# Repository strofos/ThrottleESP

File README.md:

# Z21 Throttle ESP
Z21 throttle implementation on ESP32 like a light Z21 lok maus. You might even build it on ESP8266 as there is no ESP32 specific functions used. It uses a standard variable resistor (pot) to handle the speed. Only 126 DCC steps is implemented. A 3x4 keyboard is used to navigate throw the menu and handle the functions 0 to 9. The code gets data from the Z21 asyncronous, so if you change the locomotive or the tracks gets an EStop you get notified on the throttle also. 

# Electronic Components
 1. ESP32 DEV board
 2. Nokia 5110 PCD8544 display module
 3. 5k or 10k variable resistor
 4. 3x4 keyboard
 5. 18650 single cell as power suply

# Flash the code
Use a standard Arduino IDE to flash the code. Just make sure you have the correct board selected and install the graphic libraries from Adafruit. I used a Nokia 5110 display, PCD8544 chipset, SPI driven, so is easy to adapt it to another SPI display.  

# Setup the Wifi
The wifi SSID and password are set inside the Config.h file. Just edit it and put your own settings.

# TCP commands
The IP can be found in the menu of the throttle, goto Menu (hold * for 1 sec) and then select Wifi (press 2). The default port is 5983. The open Putty, add the IP and port and then select Telnet. If successful a command promt will apear. You can now send the desired command to the throttle.
Here is the complete list of commands implemented on the throttle:
- &lt;loco adr="45"> -> lock the loco address to 45. change the 45 to the desired address
- &lt;loco adr="*">  -> unlock the loco address menu. the address can be changed
- &lt;lock>          -> locks the maus, all actions are suspended
- &lt;unlock>        -> unlocks/frees the maus; also <loco> commands can be used

# How to make the enclosure
After you print the Top and Bottom enclosure parts on a standard 3D filament printer you need some M3 insert-threads and M3 standard screws to put it all together. See the images for more information. I test-printed them on my Anycubic Kobra S1 3D printer. The 18650 cell lid is still under design so it is missing from the current repo.

# Copyright
Fell free to download, make and share this project! A like or share of this repo will be much appreciated!

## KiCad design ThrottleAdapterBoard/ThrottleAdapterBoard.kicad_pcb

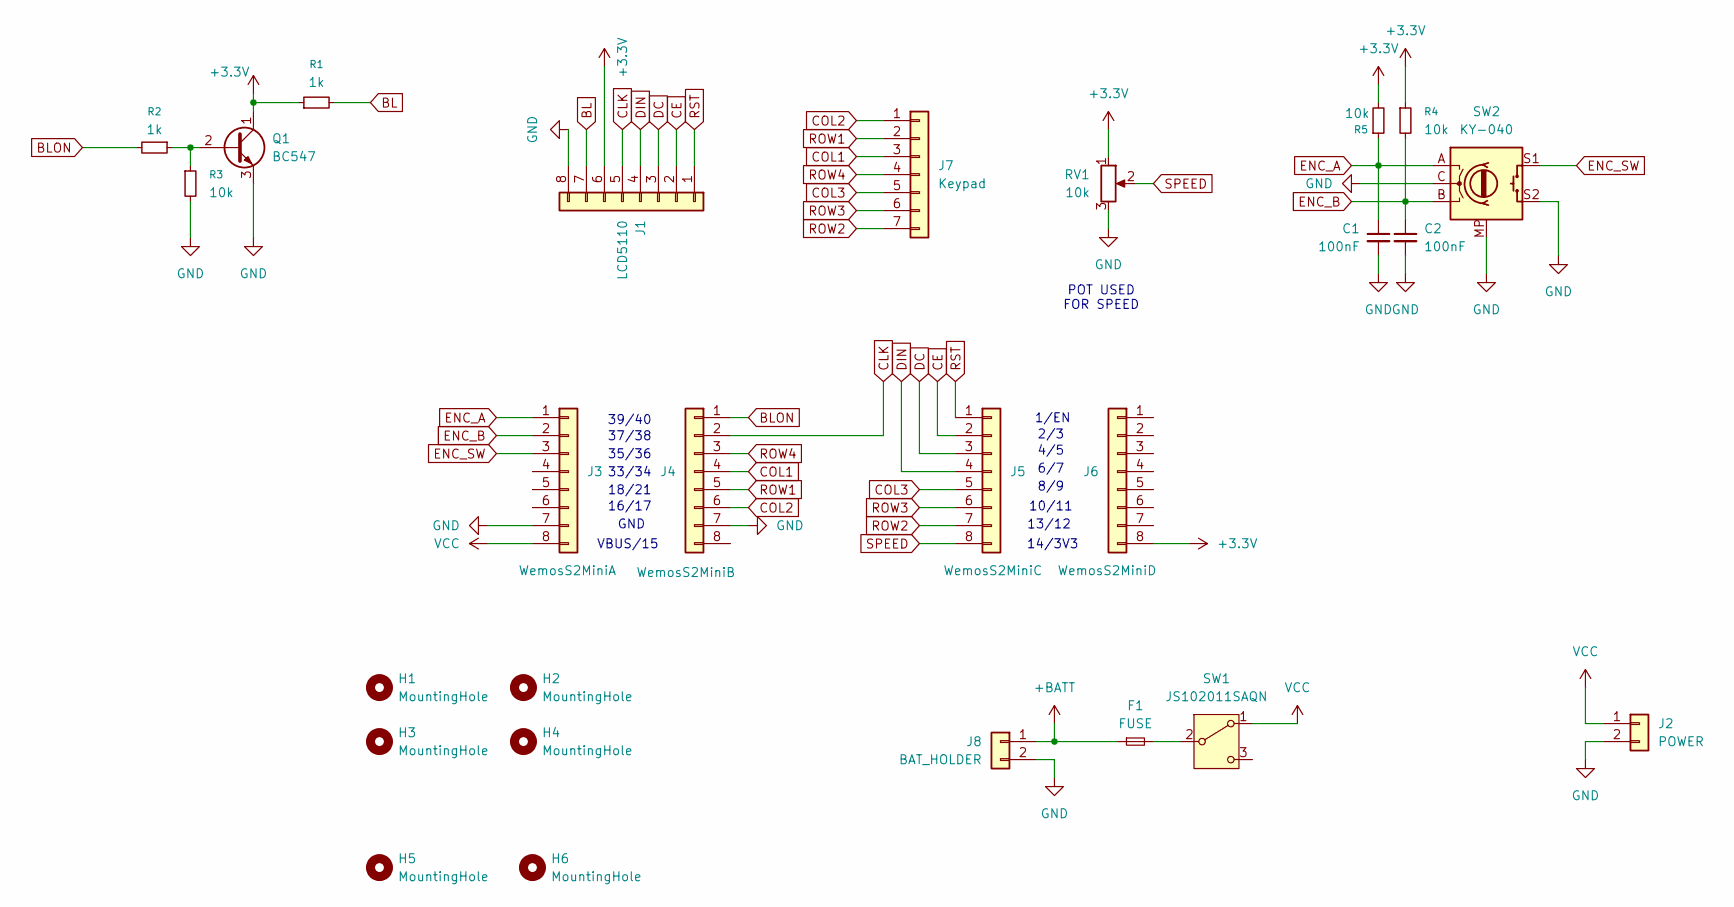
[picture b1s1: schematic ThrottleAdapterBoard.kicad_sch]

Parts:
C1, C2: 100nF; C_1210_3225Metric_Pad1.33x2.70mm_HandSolder
F1: FUSE; R_1206_3216Metric_Pad1.30x1.75mm_HandSolder
H1, H2, H3, H4, H5, H6: MountingHole; MountingHole_3.7mm
J1: LCD5110; PinHeader_1x08_P2.54mm_Vertical
J2: POWER; Altech_AK100_1x02_P5.00mm
J3: WemosS2MiniA; PinHeader_1x08_P2.54mm_Vertical
J4: WemosS2MiniB; PinHeader_1x08_P2.54mm_Vertical
J5: WemosS2MiniC; PinHeader_1x08_P2.54mm_Vertical
J6: WemosS2MiniD; PinHeader_1x08_P2.54mm_Vertical
J7: Keypad; PinHeader_1x07_P2.54mm_Vertical
J8: BAT_HOLDER; BatteryHolder_18650_THT
Q1: BC547; TO-92_Inline_Horizontal1
R1, R2: 1k; R_1206_3216Metric_Pad1.30x1.75mm_HandSolder
R3, R4, R5: 10k; R_1206_3216Metric_Pad1.30x1.75mm_HandSolder
RV1: 10k; Altech_AK100_1x03_P5.00mm
SW1: JS102011SAQN; SW_SPDT_CK_JS102011SAQN
SW2: KY-040; RotaryEncoder_Alps_EC12E-Switch_Vertical_H20mm_CircularMoun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

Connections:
+3.3V: J1.6, J6.8 (Pin_8_8), Q1.1 (C), R1.1, R4.1, R5.2, RV1.1
+BATT: F1.1, J8.1
BL: J1.7, R1.2
BLON: J4.1, R2.2
CE: J1.2, J5.2
CLK: J1.5, J4.2
COL1: J4.4, J7.3
COL2: J4.6, J7.1
COL3: J5.5, J7.5
DC: J1.3, J5.3
DIN: J1.4, J5.4
ENC_A: C1.1, J3.1, R5.1, SW2.A
ENC_B: C2.1, J3.2, R4.2, SW2.B
ENC_SW: J3.3, SW2.S1
GND: C1.2, C2.2, J1.8, J2.2, J3.7, J4.7, J8.2, Q1.3 (E), R3.2, RV1.3, SW2.C, SW2.MP, SW2.S2
unnamed: Q1.2 (B), R2.1, R3.1
unnamed: F1.2, SW1.2 (B)
ROW1: J4.5, J7.2
ROW2: J5.7, J7.7
ROW3: J5.6, J7.6
ROW4: J4.3, J7.4
RST: J1.1, J5.1
SPEED: J5.8, RV1.2
VCC: J2.1, J3.8, SW1.1 (A)

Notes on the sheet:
14/3V3
33/34
VBUS/15
10/11
4/5
16/17
GND
37/38
2/3
35/36
8/9
6/7
13/12
POT USED FOR SPEED
18/21
39/40
1/EN

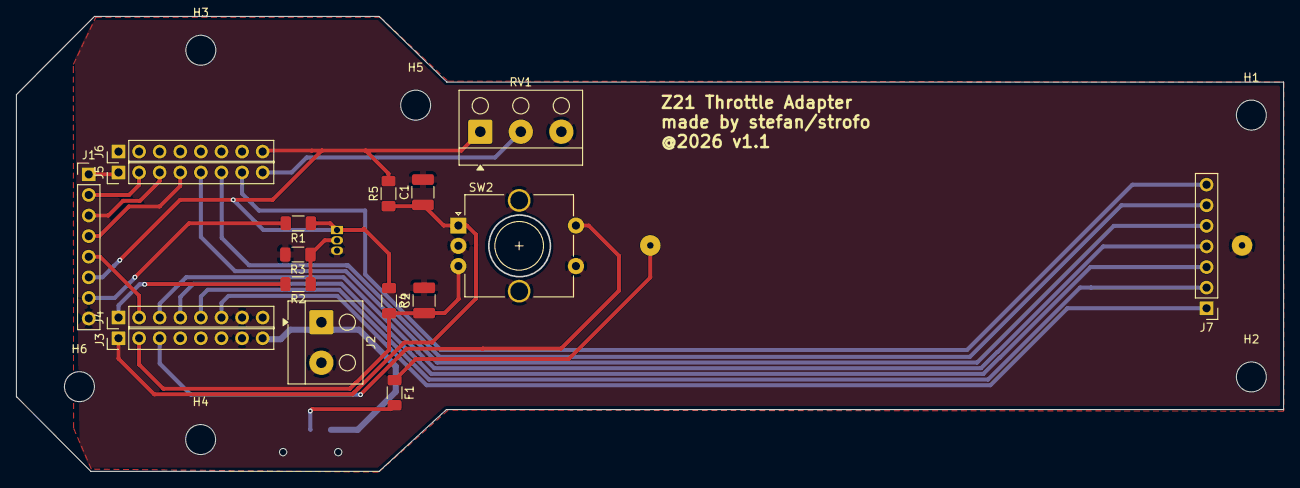
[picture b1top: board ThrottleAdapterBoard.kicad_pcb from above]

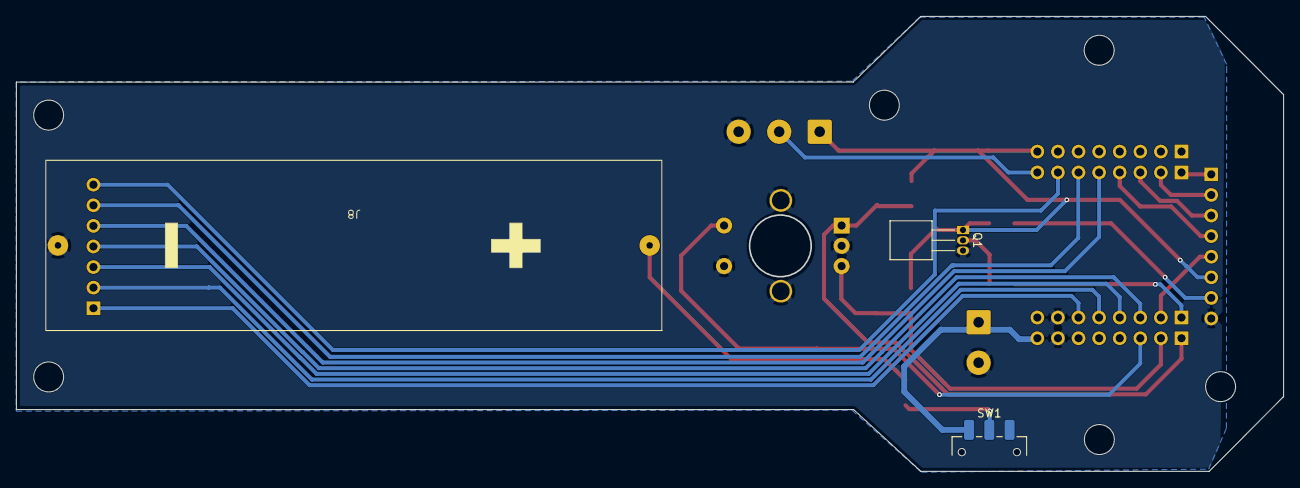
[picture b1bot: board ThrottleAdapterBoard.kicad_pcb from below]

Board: 2 copper layers, 156.2 x 56.0 mm, 26 parts (3 on the bottom side), 24 nets.

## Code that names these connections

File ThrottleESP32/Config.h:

#ifndef CONFIG_H
#define CONFIG_H
#include <WiFi.h>
#include <WiFiUdp.h>

//#define ESP32_NODE
#define ESP32_D1MINI_S2 

#ifdef ESP32_NODE
  #define LCD_RST   22
  #define LCD_CE    21
  #define LCD_DC    19
  #define LCD_DIN   18
  #define LCD_CLK    5
  #define POT_PIN   34
    
  // C2 R1 C1 R4 C3 R3 R2
  #define COL1      27
  #define COL2      12
  #define COL3      25
  #define ROW1      14
  #define ROW2      32
  #define ROW3      33
  #define ROW4      26
#else
  #define LCD_RST   1
  #define LCD_CE    2
  #define LCD_DC    4
  #define LCD_DIN   6
  #define LCD_CLK   38
  #define LCD_BL    40
  #define POT_PIN   14

  #define COL1      34
  #define COL2      17
  #define COL3       8
  #define ROW1      21
  #define ROW2      13
  #define ROW3      10
  #define ROW4      36
#endif




#define LOK_FORWARD  1
#define LOK_STOP     0
#define LOK_REVERSE -1

#define TRACK_OFF   0
#define TRACK_ON    1
#define TRACK_PROG  2
#define TRACK_ESTOP 3
#define TRACK_SHORT 8 

#define TCP_COMMANDS_PORT 8983
#define HTTP_COMMANDS_PORT 80

enum WifiState
{
  WIFI_IDLE,
  WIFI_RESET_1,
  WIFI_RESET_2,
  WIFI_RESET_3,
  WIFI_CONNECTING,
  WIFI_CONNECTED,
  WIFI_FAILED
};

extern WifiState wifiState;

#define AP_MODE_SSID "ESP32_CFRP"
#define AP_MODE_PASS "CFRPa55ing"

extern char ssid[33];
extern char password[65];

extern const IPAddress z21_ip;
extern const uint16_t z21_port;

extern WiFiUDP udp;

extern volatile uint8_t  trackPower;
extern bool     throttleLocked;
extern uint16_t locoAddr;
extern bool     locoLocked;
extern uint8_t  locoSpeed;
extern int8_t   locoDirection;
extern volatile bool locoFunctionsStates[10];

#endif

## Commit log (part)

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2026-06-07 Arduino code for ESP32
2026-06-07 Enclosure for the Throttle
2026-06-07 Enclosure design process
2026-06-07 Update README with detailed project information
    Expanded project description and added setup instructions, enclosure details, and copyright information.
2026-06-07 3D enclosure
2026-06-13 added wifi config functionalities. TCP commands for throttle lock is not working
2026-06-13 added a distancing part
2026-06-13 added TCP commands support to lock the maus or to lock it on a specific address
2026-06-13 Document TCP commands for throttle control
    Added TCP commands section with command list for throttle.
2026-06-13 Fix HTML entities in TCP commands list
    Correct HTML entity encoding for TCP commands section.
2026-06-13 Enhance TCP commands instructions in README
    Updated TCP commands section with detailed instructions on finding the IP and using Telnet.
2026-06-25 kicad board
2026-06-26 PCB Board
2026-06-26 UI updates
